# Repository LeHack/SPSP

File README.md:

# SPSP
Particulate matter pollution monitoring system (:poland: System Pomiaru Stężenia Pyłu w powietrzu)

This repository contains my bachelor of engineering project.

## Purpose

The main goal of this project was to build a standalone air/weather monitoring station while at the same time learning as much as possible about digital electronics and FPGAs.

## Overall structure and points of interest

The project is split into five parts:
* [device programming (FPGA configuration) in VHDL (Quartus Prime LE 17.2)](src/vhdl)
* [archiver and user interface in Python (3.x)](src/python)
* [device API binding for Python](src/python/API)
* [custom PCBs designed for the project (KiCad 5.x)](hardware)
* [intermediate build stages of the device programming with "unit" test benches](src/vhdl-dev)

## System architecture

## Device component layout

## Hardware used (BOM)

The measurement device was built using the following parts:

Element name | Spec | Qty
--- | --- | ---
DE0-Nano | Cyclone® IV EP4CE22F17C6N | 1 
Bluetooth module | RN4020-V/RM | 1
Humidity sensor | DHT11 | 1
Pressure sensor | LPS331AP | 1
Optical dust sensor | GP2Y1010AU0F | 1
4x8-segment display | FJ5461BH, 14mm red | 1
8 bit shift register | 74HC595 | 1
Multiplexer (3x2ch) | 74HCT4053 | 2
Tact switch | 6x6mm, h=8.0mm | 2
Electrolytic capacitor | 220uF 35V, 8x12 | 1
1206 monolithic capacitor | 100nF 50V | 1
1206 resistor |  150R, 0.25W | 1
1206 resistor |  220R, 0.25W | 4
1206 resistor |  4k7R, 0.25W | 1
PCB connector | LPH-14S/SCP-14P | 1
PCB connector | LPH-16S/SCP-16P | 1
Idc connector | FC-14, 1,27mm pitch | 2
Idc connector | FC-16, 1,27mm pitch | 2
Flat cable | 10x28AWG, 1,27mm pitch | 1 roll

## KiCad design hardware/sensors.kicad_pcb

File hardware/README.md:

# SPSP - Hardware

One of the goals of the project was to make it modular and easily fittable into a housing (in order to protect the electronics from weather elements).  
Therefore I designed two easily detachable (via flat cable) PCBs:
* sensors PCB - for all the sensors to be joined together (excluding the PM10 sensor, which is attached via a separate cable, due to the nature of PM10 measurements)

* display and comms PCB - for the display (of own design), input switches and a communications module

### Sensors

### Display and comms

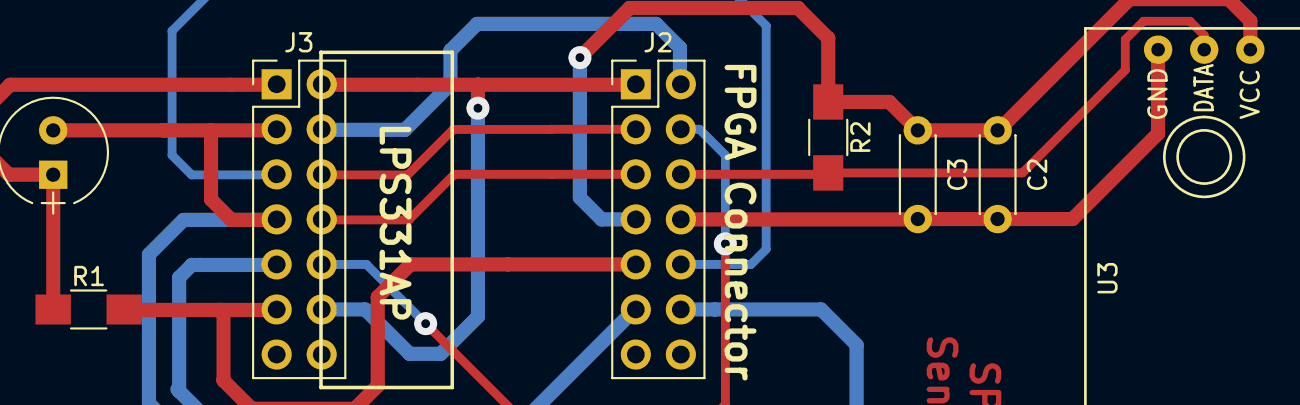
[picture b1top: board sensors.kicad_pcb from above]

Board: 2 copper layers, 8 parts (0 on the bottom side), 12 nets.

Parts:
C1: 220uF; CP_Radial_Tantal_D6.0mm_P2.50mm
C2, C3: 50nF; C_Disc_D4.3mm_W1.9mm_P5.00mm
J2, J3: Conn_02x07_Odd_Even; Pin_Header_Straight_2x07_Pitch2.54mm
R1: 150; R_1206_HandSoldering
R2: 5k; R_1206_HandSoldering
U3: DHT11

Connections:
/DHT-DATA: J2.6, R2.2, U3.2
/DHT-Vcc: C2.1, C3.1, J2.7, R2.1, U3.1
/GP2Y-LED: J2.10, J3.5
/GP2Y-V0: J2.11, J3.9
/GP2Y-Vcc: J2.9, J3.11, R1.2
/LPS-SCL: J2.5, J3.8
/LPS-SDA: J2.3, J3.6
/LPS-SDO: J2.4, J3.10
/LPS-Vin: J2.1, J3.2, J3.12
AGND: C1.2, J2.12, J3.3, J3.7
DGND: C2.2, C3.2, J2.2, J2.8, J3.4, U3.3
unnamed: C1.1, J3.1, R1.1

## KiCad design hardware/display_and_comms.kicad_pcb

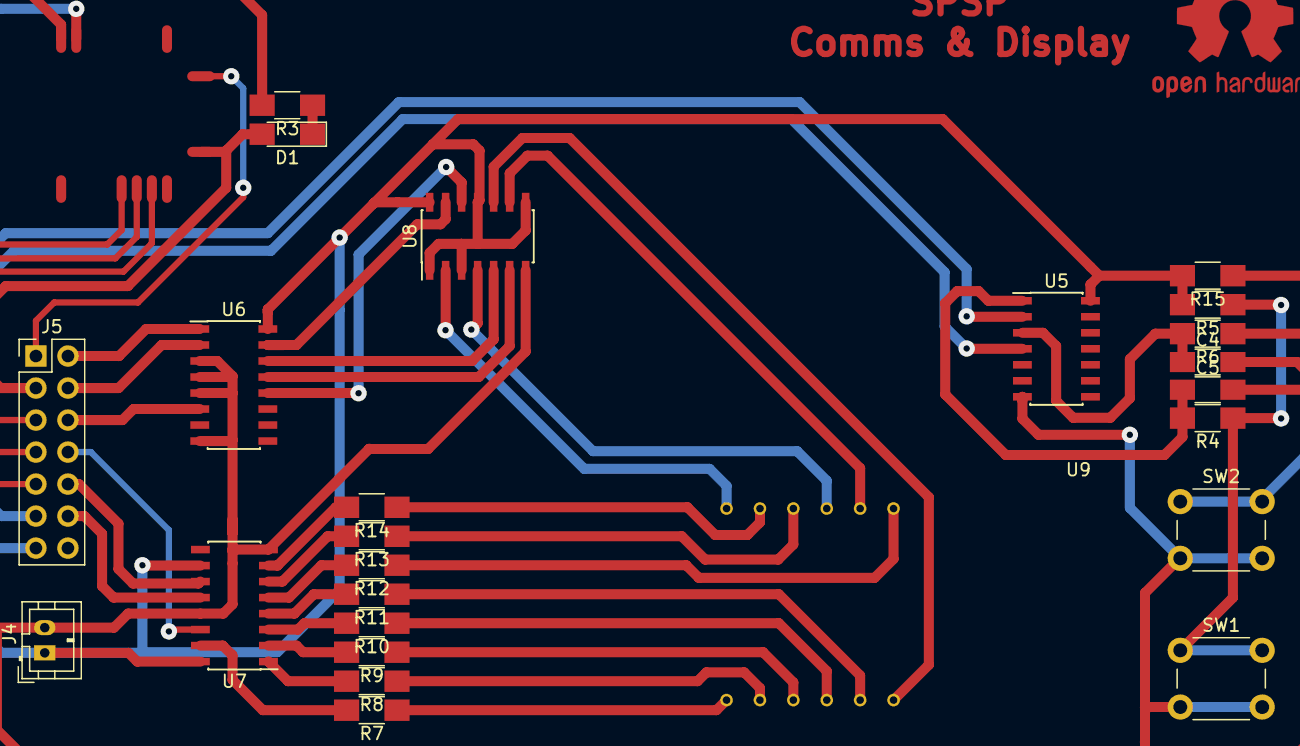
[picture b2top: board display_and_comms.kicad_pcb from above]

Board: 2 copper layers, 26 parts (0 on the bottom side), 44 nets.

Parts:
C4, C5: 100nF; C_1206_HandSoldering
D1: LED; LED_1206_HandSoldering
J4: Power; JST_PH_B2B-PH-K_02x2.00mm_Straight
J5: FPGA Connector; Pin_Header_Straight_2x07_Pitch2.54mm
R3, R7, R8, R9, R10, R11, R12, R13, R14: 220; R_1206_HandSoldering
R4, R5, R6, R15: 10k; R_1206_HandSoldering
SW1: B_PREV; SW_PUSH_6mm_h8mm
SW2: B_NEXT; SW_PUSH_6mm_h8mm
U4: RN4020
U5: 74HC14; SOIC-14_3.9x8.7mm_Pitch1.27mm
U6: 74HC238; SOIC-16_3.9x9.9mm_Pitch1.27mm
U7: 74HC595; SOIC-16_3.9x9.9mm_Pitch1.27mm
U8: 74HC4066; SOIC-14_3.9x8.7mm_Pitch1.27mm
U9: FJ-5461BH

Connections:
/DISP-A0: J5.2, U6.1
/DISP-A1: J5.4, U6.2
/DISP-DS: J5.8, U7.14
/DISP-ENA: J5.6, U6.6
/DISP-NEXT: J5.11, U5.4
/DISP-PREV: J5.13, U5.2
/DISP-SHCLK: J5.10, U7.11
/DISP-STCLK: J5.12, U7.12
/DISPRN-VDD: J4.1, R5.2, R15.2, U4.23, U5.14, U6.16, U7.10, U7.16, U8.1, U8.3, U8.8, U8.11, U8.14
/RN-PIO1: D1.2, J5.3, U4.10
/RN-UART_RX: J5.7, U4.6
/RN-UART_TX: J5.9, U4.5
/RN-WAKE_HW: J5.1, U4.15
/RN-WAKE_SW: J5.5, U4.7
DGND: C4.2, C5.2, J4.2, R3.2, SW1.2, SW2.2, U4.24, U5.7, U6.3, U6.4, U6.5, U6.8, U7.8, U7.13, U8.7
unnamed: C4.1, R6.2, U5.3
unnamed: C5.1, R4.2, U5.1
unnamed: D1.1, R3.1
unnamed: R4.1, R5.1, SW1.1
unnamed: R7.1, U9.1
unnamed: R7.2, U7.15
unnamed: R8.1, U9.2
unnamed: R8.2, U7.1
unnamed: R9.1, U9.3
unnamed: R9.2, U7.2
unnamed: R10.1, U9.4
unnamed: R10.2, U7.3
unnamed: R11.1, U9.5
unnamed: R11.2, U7.4
unnamed: R12.1, U9.7
unnamed: R12.2, U7.5
unnamed: R13.1, U9.10
unnamed: R13.2, U7.6
unnamed: R14.1, U9.11
unnamed: R14.2, U7.7
unnamed: R6.1, R15.1, SW2.1
unnamed: U6.12, U8.12
unnamed: U6.13, U8.6
unnamed: U6.14, U8.5
unnamed: U6.15, U8.13
unnamed: U8.2, U9.12
unnamed: U8.4, U9.9
unnamed: U8.9, U9.8
unnamed: U8.10, U9.6

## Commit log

2019-03-02 Sources imported from private repository.
2019-03-03 Fixed some missing parts in the setup procedure (station/params setup). Updated required versions and description.
2019-03-03 Added some UI/API description.
2019-03-03 Some description for the Python API binding (WIP).
2019-03-03 Some more docs.
2019-03-03 Changed licensing :)
2019-03-04 Demo database with some collected measurements.
2019-03-04 Added hardware projects (KiCad) and a lot of docs.
2019-03-04 Added real PCB photos. Also moved API binding diagram to API Readme.
2019-03-04 Added protocol/interface used by each driver.
2019-10-21 Bump django from 2.1.7 to 2.1.11 in /src/python
    Bumps [django](https://github.com/django/django) from 2.1.7 to 2.1.11.
    - [Release notes](https://github.com/django/django/releases)
    - [Commits](https://github.com/django/django/compare/2.1.7...2.1.11)
2020-02-11 Bump django from 2.1.7 to 2.2.10 in /src/python
    Bumps [django](https://github.com/django/django) from 2.1.7 to 2.2.10.
    - [Release notes](https://github.com/django/django/releases)
    - [Commits](https://github.com/django/django/compare/2.1.7...2.2.10)
2020-06-05 Bump django from 2.1.7 to 2.2.13 in /src/python
    Bumps [django](https://github.com/django/django) from 2.1.7 to 2.2.13.
    - [Release notes](https://github.com/django/django/releases)
    - [Commits](https://github.com/django/django/compare/2.1.7...2.2.13)
2021-06-01 Bump urllib3 from 1.24.1 to 1.26.5 in /src/python
    Bumps [urllib3](https://github.com/urllib3/urllib3) from 1.24.1 to 1.26.5.
    - [Release notes](https://github.com/urllib3/urllib3/releases)
    - [Changelog](https://github.com/urllib3/urllib3/blob/main/CHANGES.rst)
    - [Commits](https://github.com/urllib3/urllib3/compare/1.24.1...1.26.5)
    ---
    updated-dependencies:
2021-06-10 Bump django from 2.1.7 to 2.2.24 in /src/python
    Bumps [django](https://github.com/django/django) from 2.1.7 to 2.2.24.
    - [Release notes](https://github.com/django/django/releases)
    - [Commits](https://github.com/django/django/compare/2.1.7...2.2.24)
    ---
    updated-dependencies:
    - dependency-name: django
2022-12-08 Bump certifi from 2018.11.29 to 2022.12.7 in /src/python
    Bumps [certifi](https://github.com/certifi/python-certifi) from 2018.11.29 to 2022.12.7.
    - [Release notes](https://github.com/certifi/python-certifi/releases)
    - [Commits](https://github.com/certifi/python-certifi/compare/2018.11.29...2022.12.07)
    ---
    updated-dependencies:
    - dependency-name: certifi
